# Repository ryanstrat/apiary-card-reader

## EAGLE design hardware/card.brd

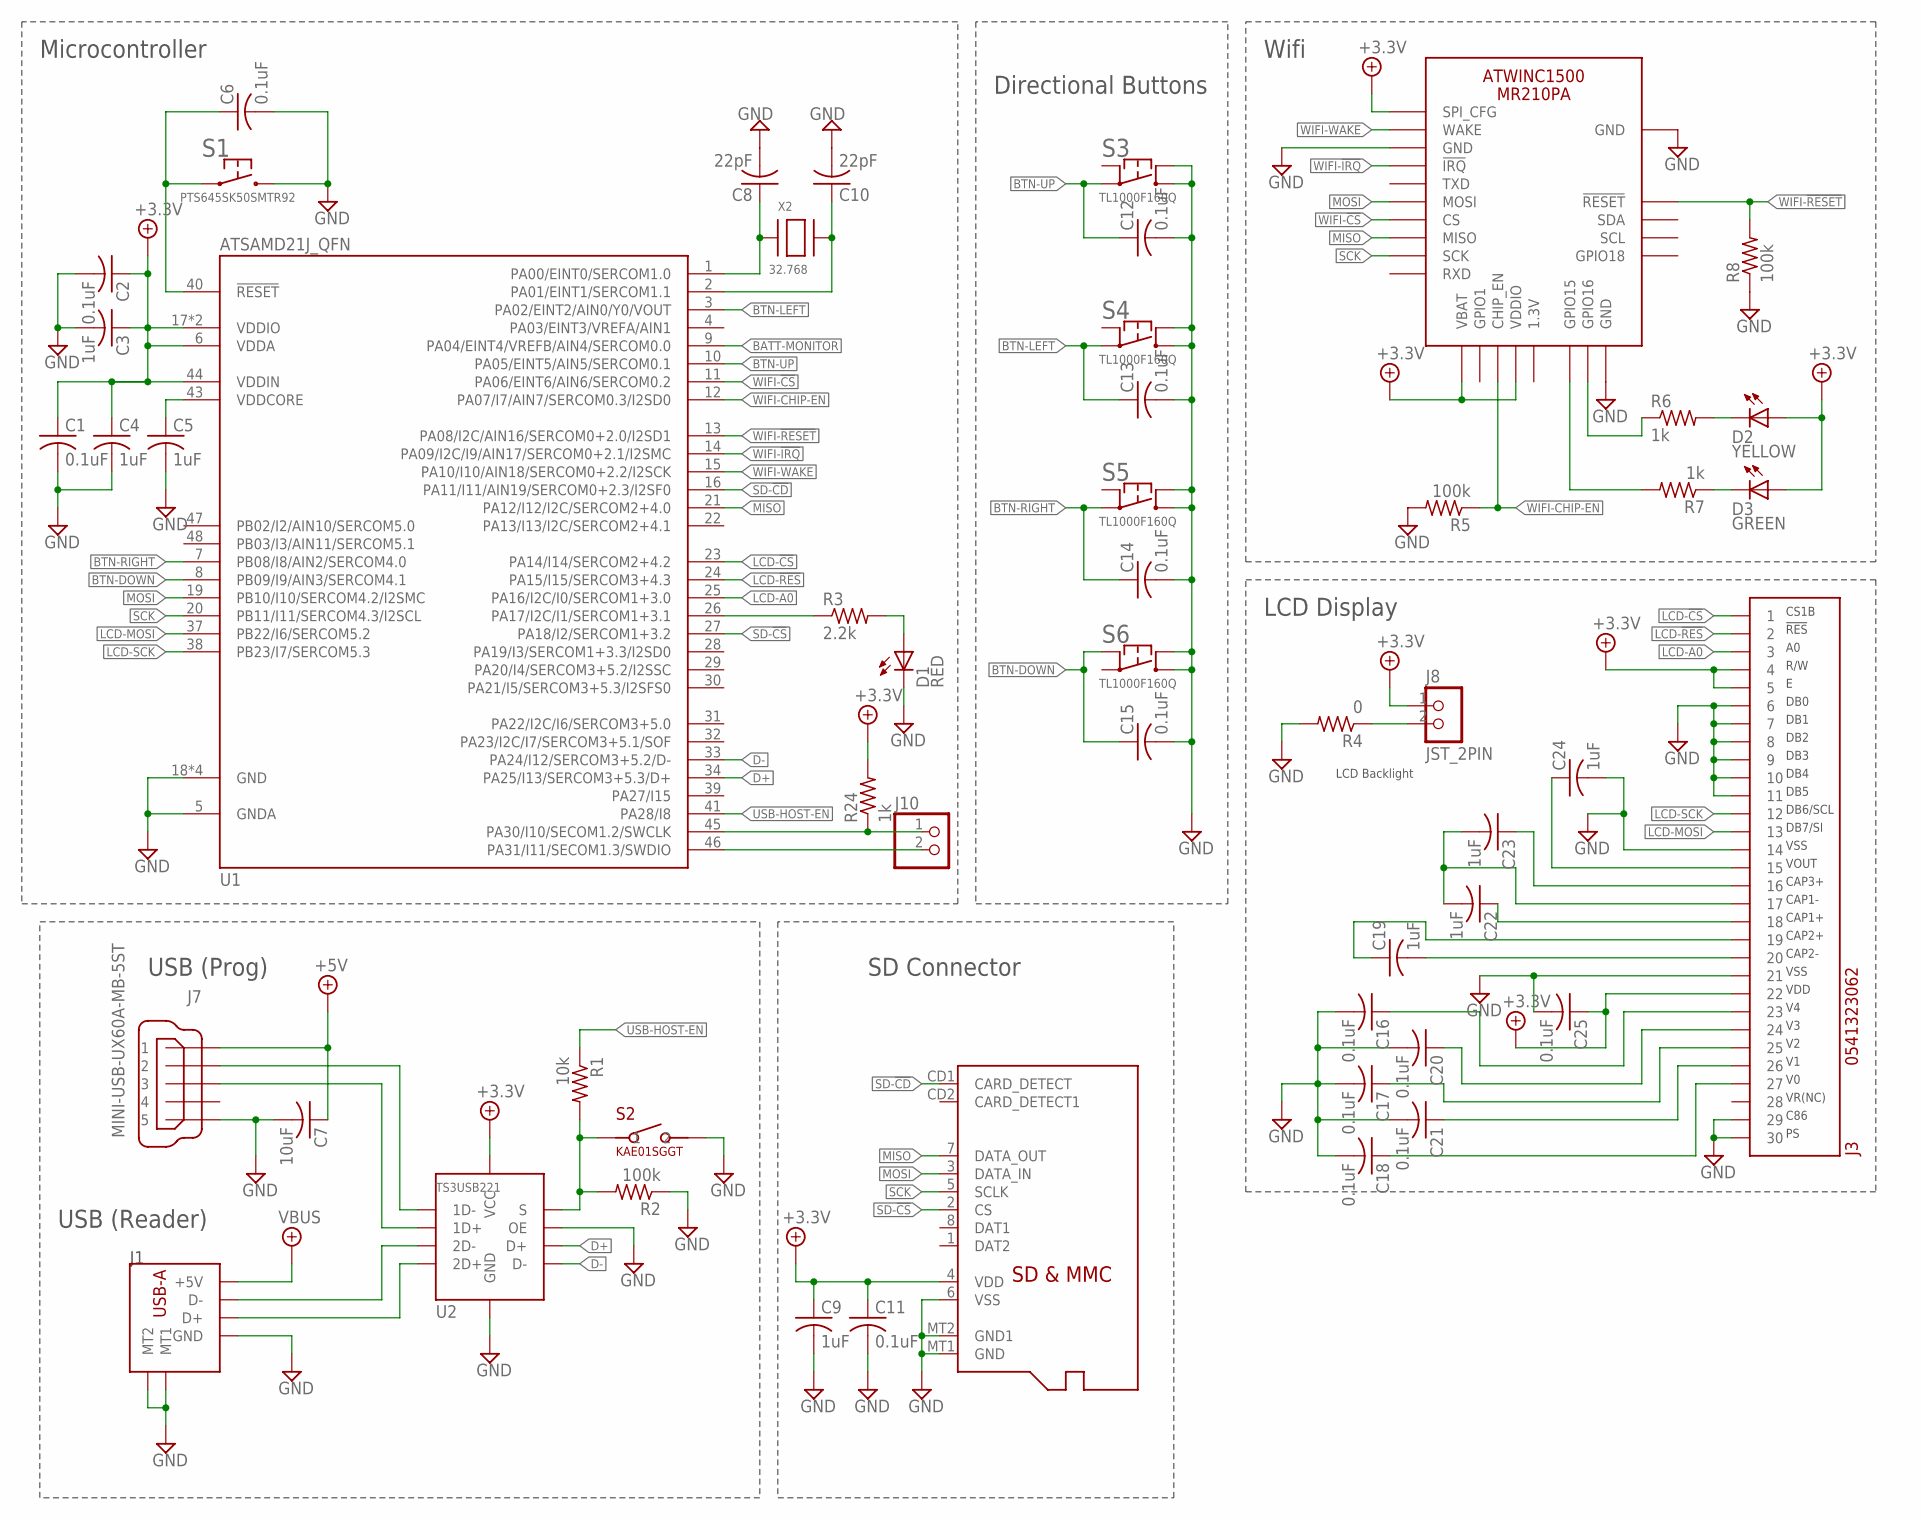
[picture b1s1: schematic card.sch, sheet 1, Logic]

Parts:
C1, C2, C6, C11, C12, C13, C14, C15, C16, C17, C18, C20, C21, C25: 0.1uF; C0603
C3, C4, C5, C9, C19, C22, C23, C24: 1uF; C0603
C7: 10uF; C0603
C8, C10: 22pF; C0603
D1: RED; CHIP-LED0603
D2: YELLOW; CHIP-LED0603
D3: GREEN; CHIP-LED0603
J1: UE27AC54100; USB-A
J2: MICROSD
J3: 0541323062
J7: MINI-USB-UX60A-MB-5ST; UX60A-MB-5ST
J8: JST_2PIN; JSTPH2
J10: CONN-2VERT; 1X2
R1: 10k; R0603
R2, R5, R8: 100k; R0603
R3: 2.2k; R0603
R4: 0; R0603
R6, R7, R24: 1k; R0603
S1: PTS645SK50SMTR92
S2: KAE01SGGT
S3, S4, S5, S6: TL1000F160Q; TL1100
U1: ATSAMD21J_QFN; TQFN48_7MM
U2: TS3USB221; 10-PIN-UQFN
X2: 32.768; XTAL3215
X3: ATWINC1500_MR210PA

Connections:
1D+: J7.3, U2.1 (1D+)
1D-: J7.2, U2.2 (1D-)
2D+: J1.3 (D+), U2.3 (2D+)
2D-: J1.2 (D-), U2.4 (2D-)
!RESET: C6.1, S1.1, S1.2 (1), U1.40 (!RESET)
+3.3V: C1.1, C2.1, C3.1, C4.1, C9.1, C11.1, C25.1, D2.A, D3.A, J2.4 (VDD), J3.4, J3.5, J3.22, J8.1, R24.2, U1.6 (VDDA), U1.17 (VDDIO), U1.36 (VDDIO), U1.44 (VDDIN), U2.10 (VCC), X3.J10 (SPI_CFG), X3.J20 (VBAT), X3.J23 (VDDIO); also elsewhere on the board
+5V: C7.1, J7.1; also elsewhere on the board
BATT-MONITOR: U1.9 (PA04/EINT4/VREFB/AIN4/SERCOM0.0); also elsewhere on the board
BTN-DOWN: C15.1, S6.2 (1B), U1.8 (PB09/I9/AIN3/SERCOM4.1)
BTN-LEFT: C13.1, S4.1 (1A), U1.3 (PA02/EINT2/AIN0/Y0/VOUT)
BTN-RIGHT: C14.1, S5.1 (1A), U1.7 (PB08/I8/AIN2/SERCOM4.0)
BTN-UP: C12.1, S3.1 (1A), U1.10 (PA05/EINT5/AIN5/SERCOM0.1)
D+: U1.34 (PA25/I13/SERCOM3+5.3/D+), U2.8 (D+)
D-: U1.33 (PA24/I12/SERCOM3+5.2/D-), U2.7 (D-)
GND: C1.2, C2.2, C3.2, C4.2, C5.2, C6.2, C7.2, C8.2, C9.2, C10.2, C11.2, C12.2, C13.2, C14.2, C15.2, C16.2, C17.2, C18.2, C20.2, C21.2, C24.2, C25.2, D1.C (K), J1.4 (GND), J1.MT1, J1.MT2, J2.6 (VSS), J2.MT1 (GND), J2.MT2 (GND1), J3.6, J3.7, J3.8, J3.9, J3.10, J3.11, J3.14, J3.21, J3.29, J3.30, J7.5, R2.1, R4.2, R5.2, R8.1, S1.3 (2), S1.4 (2), S2.2, S3.3 (2A), S3.4 (2B), S4.3 (2A), S4.4 (2B), S5.3 (2A), S5.4 (2B), S6.3 (2A), S6.4 (2B), U1.5 (GNDA), U1.18 (GND), U1.35 (GND), U1.42 (GND), U1.THERMAL (GND), U2.5 (GND), U2.6 (OE), X3.J9 (GND), X3.J12 (GND), X3.J28 (GND); also elsewhere on the board
LCD-!CS: J3.1, U1.23 (PA14/I14/SERCOM2+4.2)
LCD-!RES: J3.2, U1.24 (PA15/I15/SERCOM3+4.3)
LCD-A0: J3.3, U1.25 (PA16/I2C/I0/SERCOM1+3.0)
LCD-CA1+: C22.1, J3.18
LCD-CA1-: C22.2, C23.2, J3.17
LCD-CA2+: C19.1, J3.19
LCD-CA2-: C19.2, J3.20
LCD-CA3+: C23.1, J3.16
LCD-K: J8.2, R4.1
LCD-MOSI: J3.13, U1.37 (PB22/I6/SERCOM5.2)
LCD-SCK: J3.12, U1.38 (PB23/I7/SERCOM5.3)
LCD-V0: C18.1, J3.27
LCD-V1: C21.1, J3.26
LCD-V2: C17.1, J3.25
LCD-V3: C20.1, J3.24
LCD-V4: C16.1, J3.23
LCD-VOUT: C24.1, J3.15
MISO: J2.7 (DATA_OUT), U1.21 (PA12/I12/I2C/SERCOM2+4.0), X3.J17 (MISO)
MOSI: J2.3 (DATA_IN), U1.19 (PB10/I10/SERCOM4.2/I2SMC), X3.J15 (MOSI)
PROG-LED: D1.A, R3.2
PROG-LED-2: R3.1, U1.26 (PA17/I2C/I1/SERCOM1+3.1)
SCK: J2.5 (SCLK), U1.20 (PB11/I11/SERCOM4.3/I2SCL), X3.J18 (SCK)
SD-!CD: J2.CD1 (CARD_DETECT), U1.16 (PA11/I11/AIN19/SERCOM0+2.3/I2SF0)
SD-!CS: J2.2 (CS), U1.27 (PA18/I2/SERCOM1+3.2)
SWCLK: J10.1, R24.1, U1.45 (PA30/I10/SECOM1.2/SWCLK)
SWDIO: J10.2, U1.46 (PA31/I11/SECOM1.3/SWDIO)
USB-HOST-EN: R1.1, U1.41 (PA28/I8)
USB-S: R1.2, R2.2, S2.1, U2.9 (S)
VBUS: J1.1 (+5V); also elsewhere on the board
VDDCORE: C5.1, U1.43 (VDDCORE)
WIFI-!CS: U1.11 (PA06/EINT6/AIN6/SERCOM0.2), X3.J16 (CS)
WIFI-!IRQ: U1.14 (PA09/I2C/I9/AIN17/SERCOM0+2.1/I2SMC), X3.J13 (!IRQ)
WIFI-!RESET: R8.2, U1.13 (PA08/I2C/AIN16/SERCOM0+2.0/I2SD1), X3.J4 (!RESET)
WIFI-CHIP-EN: R5.1, U1.12 (PA07/I7/AIN7/SERCOM0.3/I2SD0), X3.J22 (CHIP_EN)
WIFI-GPIO15: R7.2, X3.J26 (GPIO15)
WIFI-GPIO16: R6.1, X3.J27 (GPIO16)
WIFI-LED-G: D3.C (K), R7.1
WIFI-LED-Y: D2.C (K), R6.2
WIFI-WAKE: U1.15 (PA10/I10/AIN18/SERCOM0+2.2/I2SCK), X3.J11 (WAKE)
X3-1: C8.1, U1.1 (PA00/EINT0/SERCOM1.0), X2.P$1
X3-2: C10.1, U1.2 (PA01/EINT1/SERCOM1.1), X2.P$2

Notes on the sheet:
Microcontroller
USB (Prog)
SD Connector
USB (Reader)
Wifi
Directional Buttons
CS1B
!RES
R/W
DB0
DB1
DB2
DB3
DB4
DB5
DB6/SCL
DB7/SI
VSS
VOUT
CAP3+
CAP1-
CAP1+
CAP2+
CAP2-
VDD
VR(NC)
C86
LCD Display
LCD Backlight

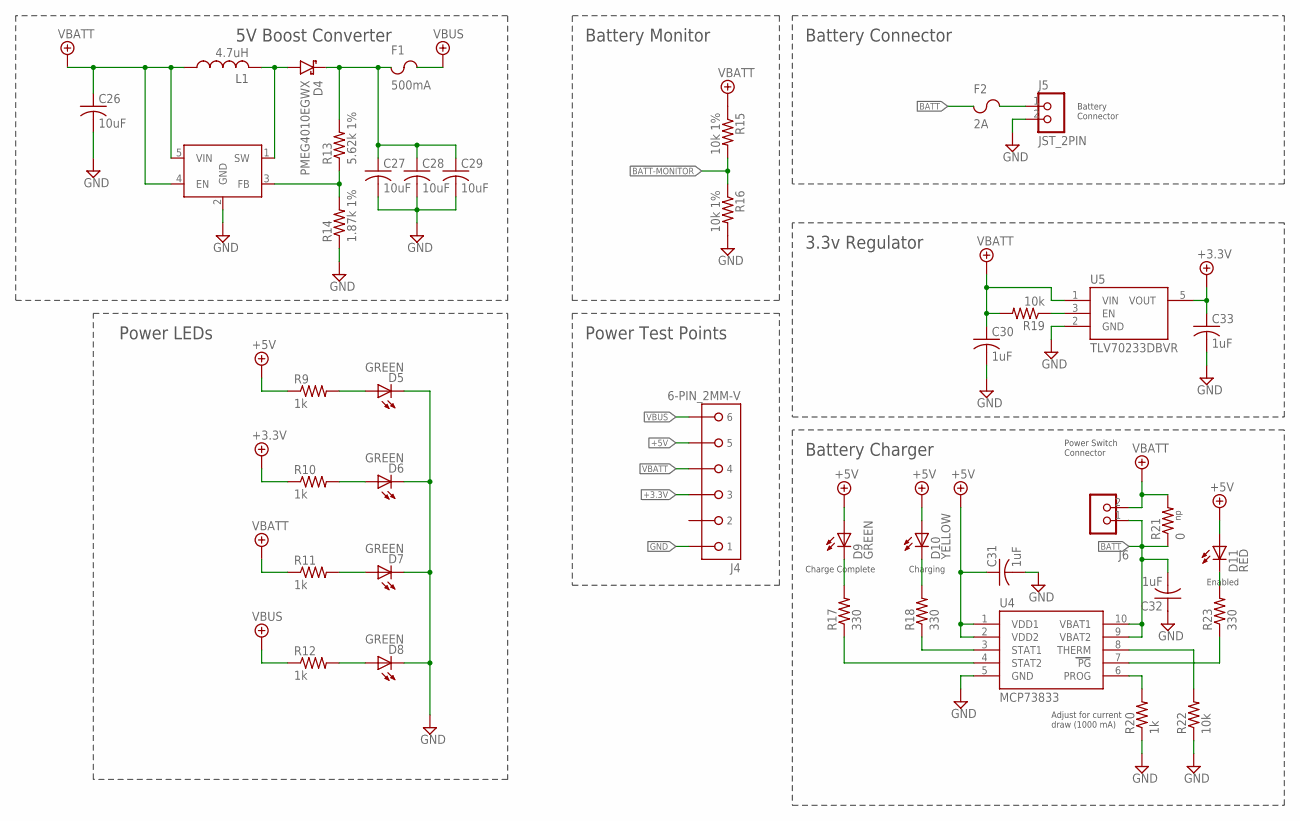
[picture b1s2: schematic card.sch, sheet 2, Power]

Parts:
C26, C27, C28, C29: 10uF; C0603
C30, C31, C32, C33: 1uF; C0603
D4: PMEG4010EGWX; SOD123
D5, D6, D7, D8, D9: GREEN; CHIP-LED0603
D10: YELLOW; CHIP-LED0603
D11: RED; CHIP-LED0603
F1: 500mA; F0603
F2: 2A; F0603
J4: 6-PIN_2MM-V; 2MM-6-V
J5, J6: JST_2PIN; JSTPH2
L1: 4.7uH; L0805
R9, R10, R11, R12, R20: 1k; R0603
R13: 5.62k 1%; R0603
R14: 1.87k 1%; R0603
R15, R16: 10k 1%; R0603
R17, R18, R23: 330; R0603
R19, R22: 10k; R0603
R21: 0; R0603
U3: MIC2288YD5-TR; TSOT-23-5
U4: MCP73833; MSOP10
U5: TLV70233DBVR; SOT-23-5

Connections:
3V3_EN: R19.1, U5.3 (EN)
+3.3V: C33.1, J4.3, R10.1, U5.5 (VOUT); also elsewhere on the board
+5V: C31.1, D9.A, D10.A, D11.A, J4.5, R9.1, U4.1 (VDD1), U4.2 (VDD2); also elsewhere on the board
BATT: C32.2, F2.1, J6.1, R21.1, U4.9 (VBAT2), U4.10 (VBAT1)
BATT-MONITOR: R15.2, R16.1; also elsewhere on the board
BATT-PRE-FUSE: F2.2, J5.1
BOOST_FB: R13.1, R14.2, U3.3 (FB)
BOOST_OUTPUT: C27.1, C28.1, C29.1, D4.C, F1.1, R13.2
BOOST_SW: D4.A, L1.2, U3.1 (SW)
CHRG-!PG: R23.1, U4.7 (PG)
CHRG-PROG: R20.2, U4.6 (PROG)
CHRG-STAT1: R18.1, U4.3 (STAT1)
CHRG-STAT2: R17.1, U4.4 (STAT2)
CHRG-THERM: R22.2, U4.8 (THERM)
GND: C26.2, C27.2, C28.2, C29.2, C30.2, C31.2, C32.1, C33.2, D5.C (K), D6.C (K), D7.C (K), D8.C (K), J4.1, J5.2, R14.1, R16.2, R20.1, R22.1, U3.2 (GND), U4.5 (GND), U5.2 (GND); also elsewhere on the board
LED-3V3: D6.A, R10.2
LED-5V: D8.A, R12.2
LED-!PG: D11.C (K), R23.2
LED-STAT1: D10.C (K), R18.2
LED-STAT2: D9.C (K), R17.2
LED-VBATT: D7.A, R11.2
LED-VBUS: D5.A, R9.2
VBATT: C26.1, C30.1, J4.4, J6.2, L1.1, R11.1, R15.1, R19.2, R21.2, U3.4 (EN), U3.5 (VIN), U5.1 (VIN)
VBUS: F1.2, J4.6, R12.1; also elsewhere on the board

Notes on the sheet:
Adjust for current draw (1000 mA)
Battery Connector
Battery Connector
3.3v Regulator
Battery Charger
Battery Monitor
Power Switch Connector
5V Boost Converter
Power Test Points
Charge Complete
Charging
Enabled
Power LEDs

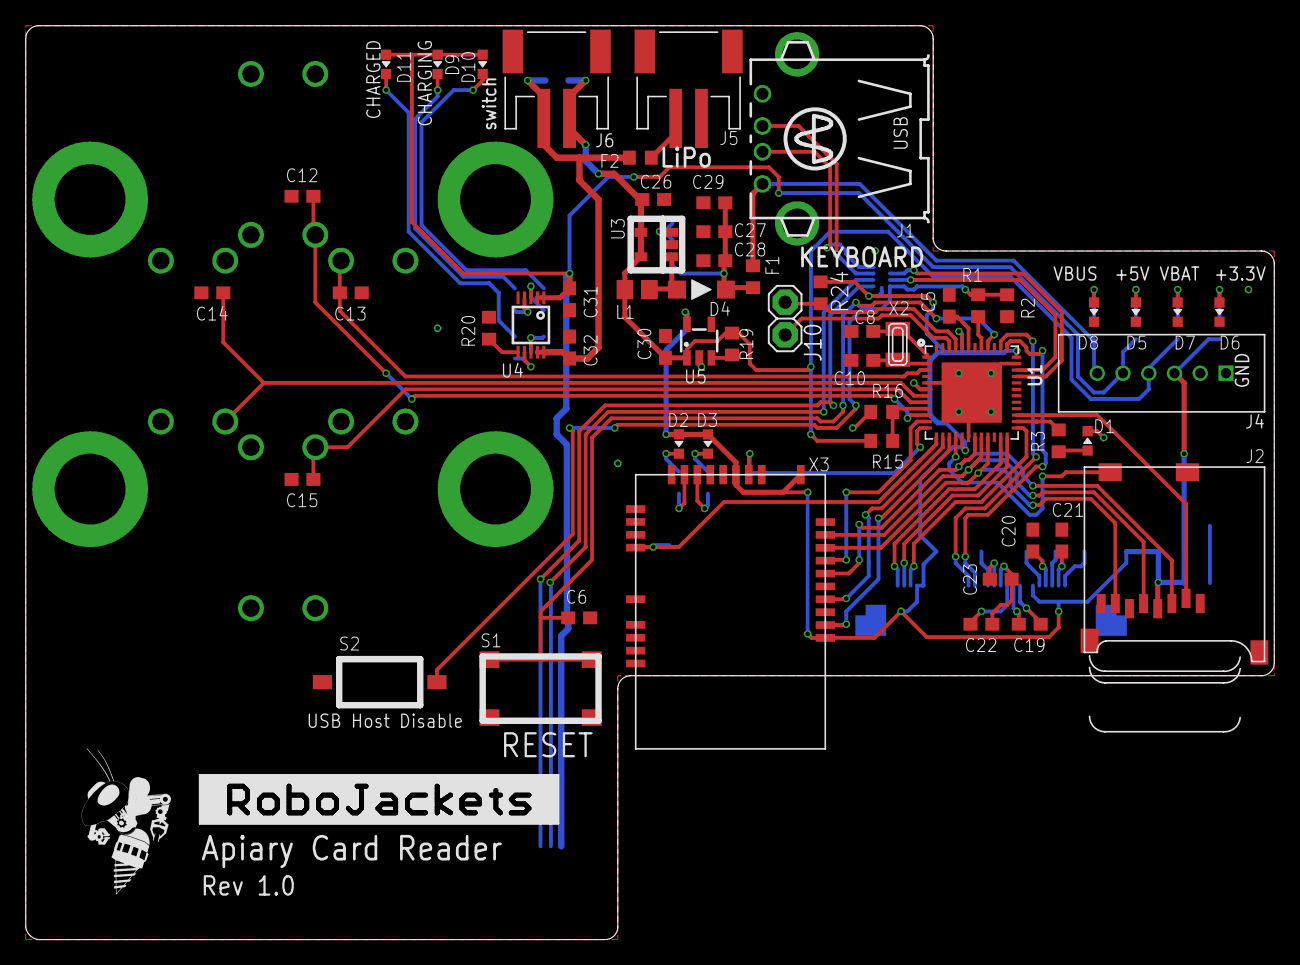
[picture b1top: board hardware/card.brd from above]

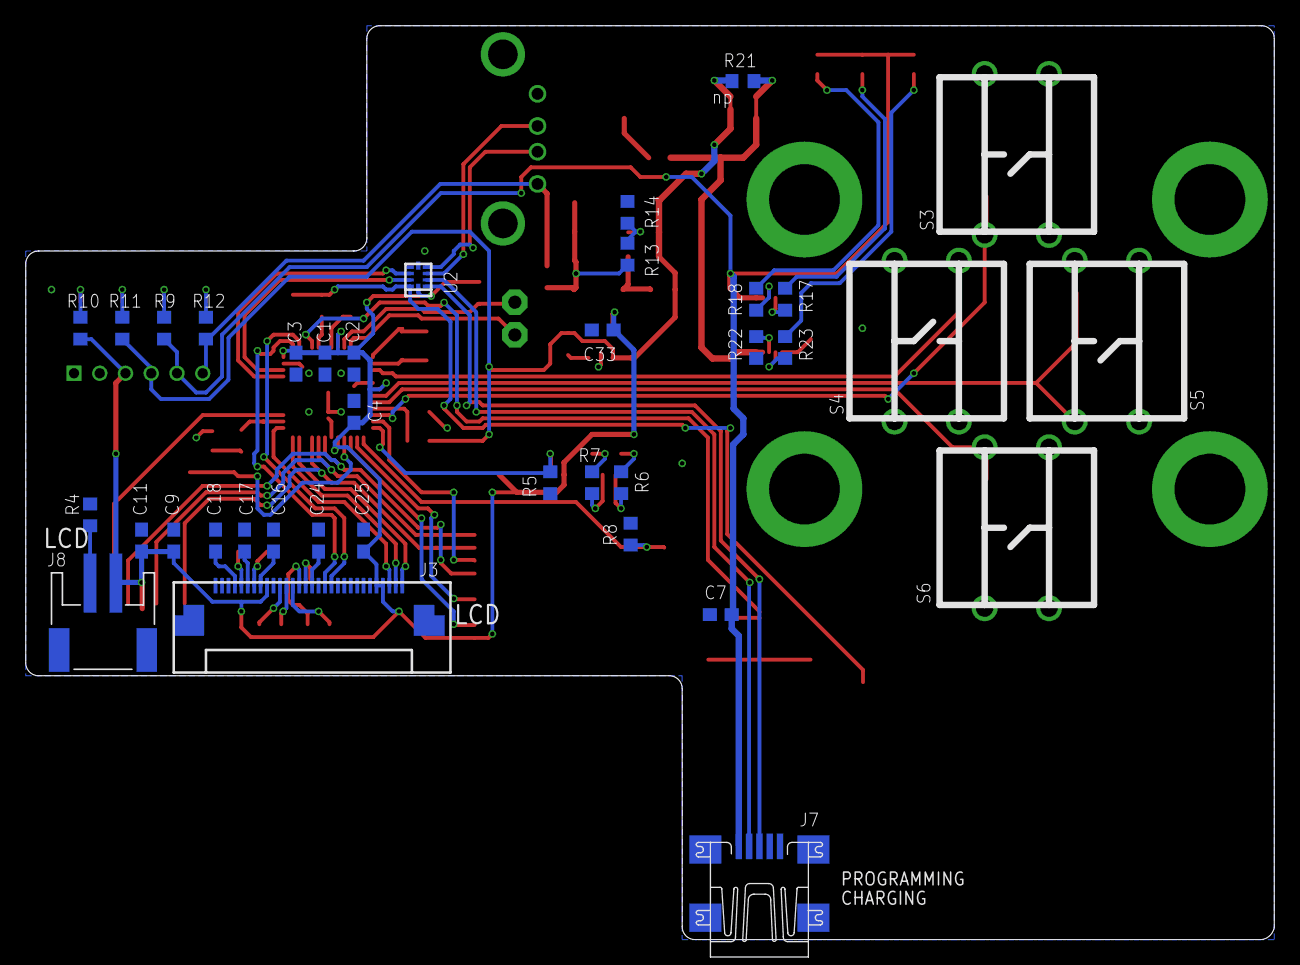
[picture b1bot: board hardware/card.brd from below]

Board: 2 copper layers, 97.0 x 71.0 mm, 95 parts (37 on the bottom side), 75 nets.

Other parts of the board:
U$1: ROBOBUZZ_0.6X
U$2: ROBOJACKETS

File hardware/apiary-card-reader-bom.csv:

"Qty";"Value";"Device";"Package";"Parts";"Description";"";
"2";"0";"R-US_R0603";"R0603";"R4, R21";"RESISTOR, American symbol";"";
"14";"0.1uF";"C-USC0603";"C0603";"C1, C2, C6, C11, C12, C13, C14, C15, C16, C17, C18, C20, C21, C25";"CAPACITOR, American symbol";"";
"1";"0541323062";"0541323062";"0541323062";"J3";"30 Position FFC, FPC Connector Contacts, Bottom 0.020" (0.50mm) Surface Mount, Right Angle";"";
"1";"1.87k 1%";"R-US_R0603";"R0603";"R14";"RESISTOR, American symbol";"";
"3";"100k";"R-US_R0603";"R0603";"R2, R5, R8";"RESISTOR, American symbol";"";
"3";"10k";"R-US_R0603";"R0603";"R1, R19, R22";"RESISTOR, American symbol";"";
"2";"10k 1%";"R-US_R0603";"R0603";"R15, R16";"RESISTOR, American symbol";"";
"4";"10uF";"C-USC0603";"C0603";"C26, C27, C28, C29";"CAPACITOR, American symbol";"";
"1";"10uF";"C-USC0805";"C0805";"C7";"CAPACITOR, American symbol";"";
"7";"1k";"R-US_R0603";"R0603";"R6, R7, R9, R10, R11, R12, R20";"RESISTOR, American symbol";"";
"12";"1uF";"C-USC0603";"C0603";"C3, C4, C5, C9, C19, C22, C23, C24, C30, C31, C32, C33";"CAPACITOR, American symbol";"";
"1";"2.2k";"R-US_R0603";"R0603";"R3";"RESISTOR, American symbol";"";
"2";"22pF";"C-USC0603";"C0603";"C8, C10";"CAPACITOR, American symbol";"";
"1";"2A";"CHIP_FUSE0603";"F0603";"F2";"";"";
"1";"32.768";"XTAL-3.2X1.5";"XTAL3215";"X2";"Low cost SMT crystals, no capacitors included";"";
"3";"330";"R-US_R0603";"R0603";"R17, R18, R23";"RESISTOR, American symbol";"";
"1";"4.7uH";"L-US-0805";"L0805";"L1";"";"";
"1";"5.62k 1%";"R-US_R0603";"R0603";"R13";"RESISTOR, American symbol";"";
"1";"500mA";"CHIP_FUSE0603";"F0603";"F1";"";"";
"1";"6-PIN_2MM-V";"6-PIN_2MM-V";"2MM-6-V";"J4";"";"";
"1";"ATSAMD21J_QFN";"ATSAMD21J_QFN";"TQFN48_7MM";"U1";"";"";
"1";"ATWINC1500_MR210PA";"ATWINC1500_MR210PA";"ATWINC1500_MR210PA";"X3";"ATWINC1500_MR210PA wifi module";"";
"1";"B2PS-VH(LF)(SN)";"B2PS-VH(LF)(SN)";"B2PS-CENTERED";"J6";"Power Connector";"";
"6";"GREEN";"LED-SMD-GREEN";"CHIP-LED0603";"D3, D5, D6, D7, D8, D9";"";"";
"2";"JST_2PIN";"JST_2PIN";"JSTPH2";"J5, J8";"JST 2-Pin Right-Angle Connector";"";
"1";"KAE01SGGT";"KAE01SGGT";"KAE01SGGT";"S2";"";"";
"1";"MCP73833";"MCP73833";"MSOP10";"U4";"Lithium-Polymer/Lithium-Ion Battery Charger [Part No.]";"";
"1";"MIC2288YD5-TR";"MIC2288YD5-TR";"TSOT-23-5";"U3";"Boost Switching Regulator IC Positive Adjustable 2.5V 1 Output 1.2A (Switch) SOT-23-5 Thin, TSOT-23-5";"";
"1";"MICROSD";"MICROSD";"MICROSD";"J2";"Micro-SD / Transflash card holder with SPI pinout";"";
"1";"MINI-USB-UX60A-MB-5ST";"MINI-USB-UX60A-MB-5ST";"UX60A-MB-5ST";"J7";"MINI USB Connector";"";
"1";"PMEG4010EGWX";"SCHOTTKEY-DIODE-SOD123";"SOD123";"D4";"";"";
"1";"PTS645SK50SMTR92";"PTS645SK50SMTR92";"PTS645SK50SMTR92";"S1";"";"";
"2";"RED";"LED-SMD-RED";"CHIP-LED0603";"D1, D11";"";"";
"4";"TL1000F160Q";"TL1000F160Q";"TL1100";"S3, S4, S5, S6";"Tactile Switch SPST-NO Top Actuated Through Hole";"";
"1";"TLV70233DBVR";"TLV70233DBVR";"SOT-23-5";"U5";"";"";
"1";"TS3USB221";"TS3USB221";"10-PIN-UQFN";"U2";"High Speed USB 2.0 1:2 MUX-DEMUX switch with single enable";"";
"1";"UE27AC54100";"UE27AC54100";"USB-A";"J1";"";"";
"2";"YELLOW";"LED-SMD-YELLOW";"CHIP-LED0603";"D2, D10";"";"";

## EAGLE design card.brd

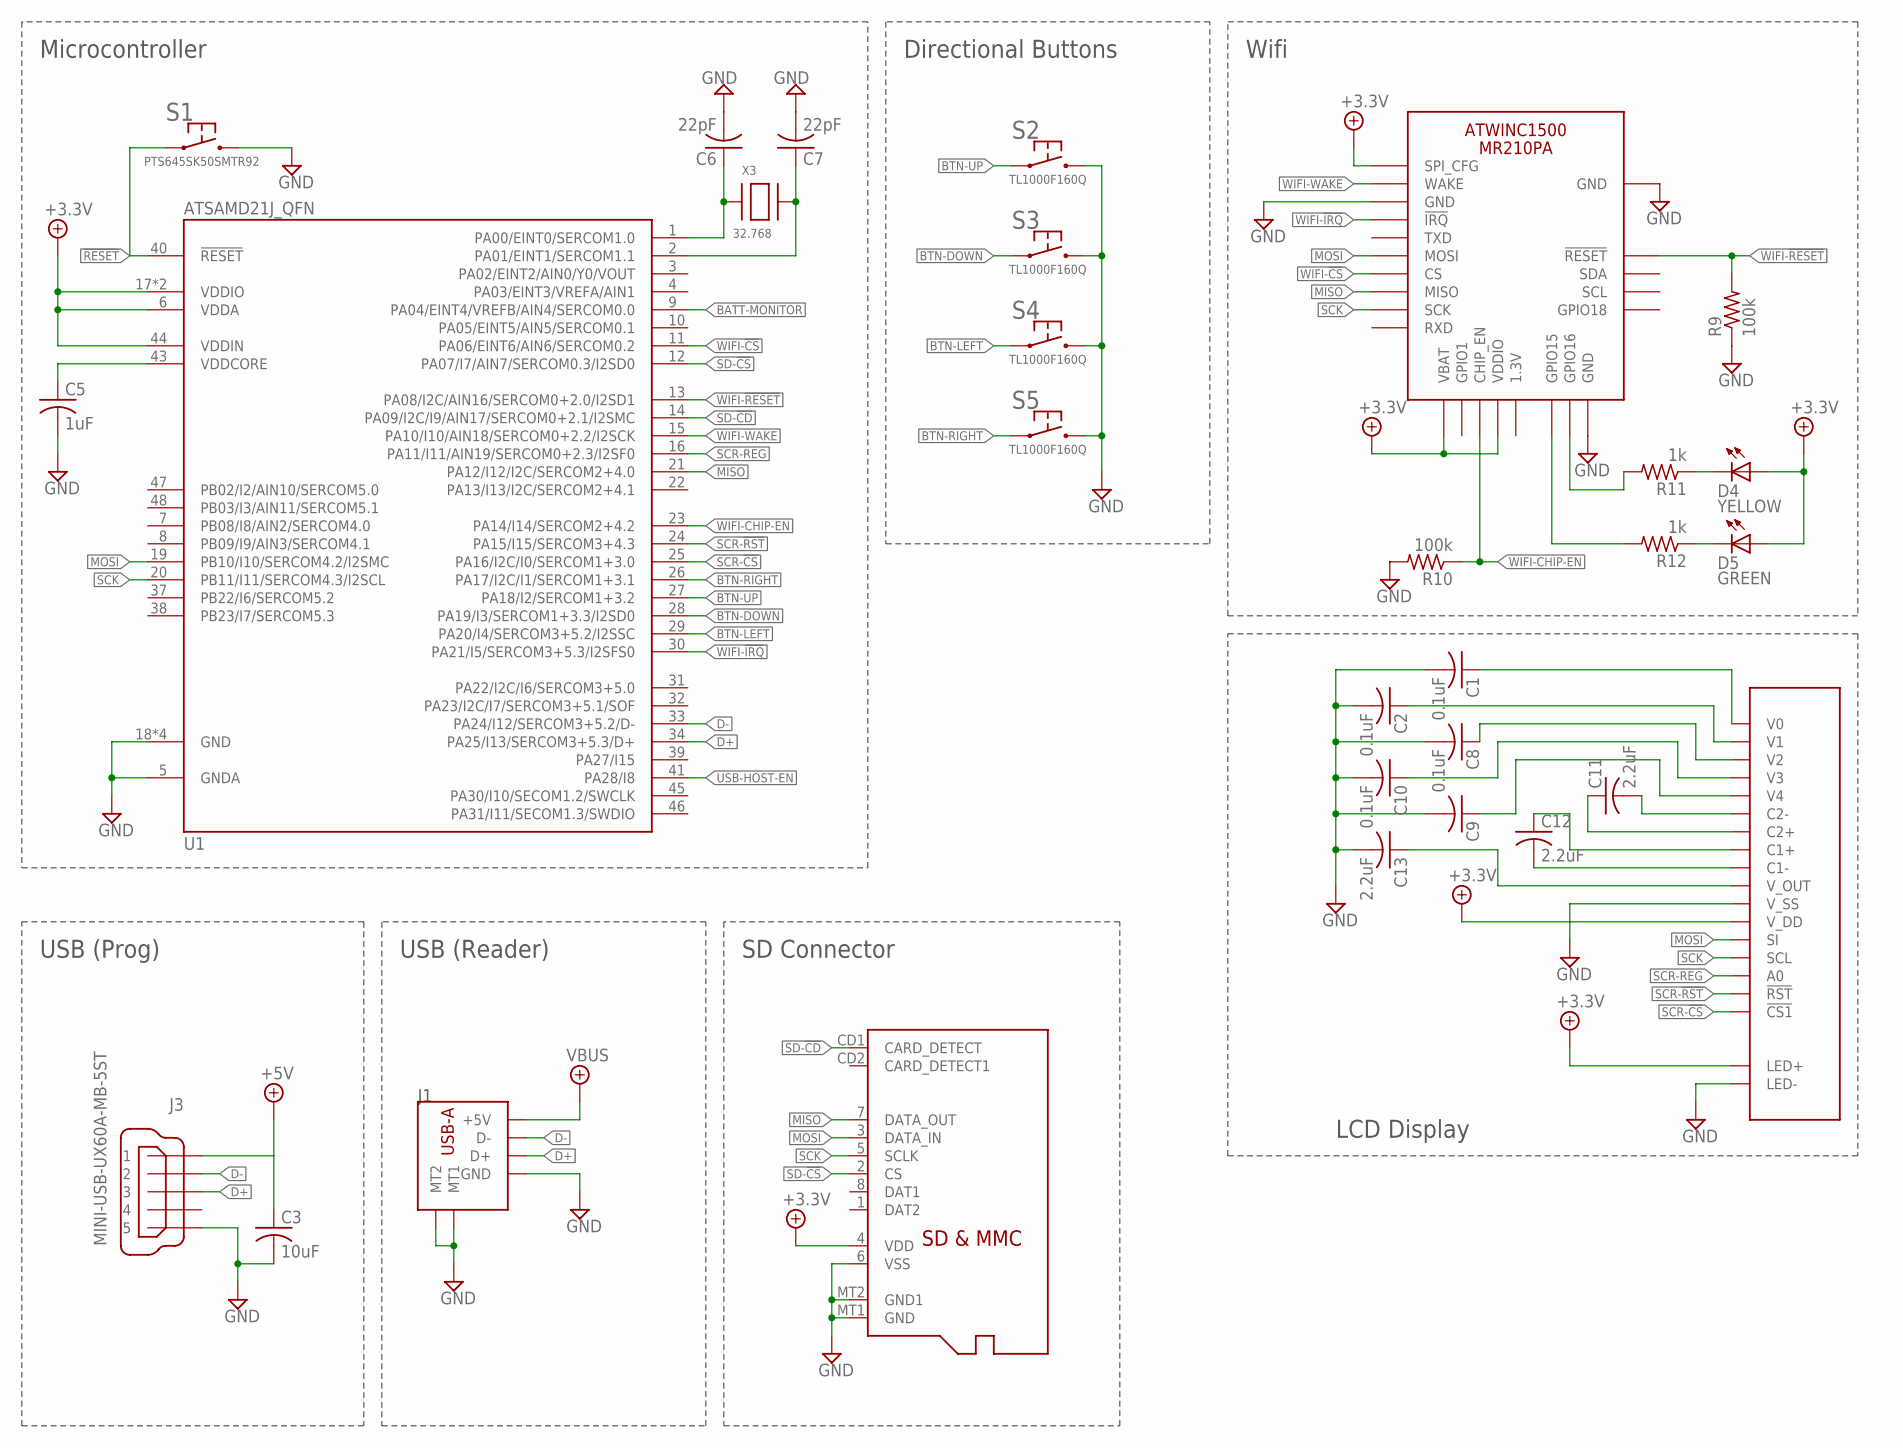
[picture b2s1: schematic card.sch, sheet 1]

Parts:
C1, C2, C8, C10: 0.1uF; C0603
C3: 10uF; C0805
C5: 1uF; C0603
C6, C7: 22pF; C0603
C9: C-USC0603; C0603
C11, C12, C13: 2.2uF; C0603
D4: YELLOW; SMARTLED-TTW
D5: GREEN; SMARTLED-TTW
J1: UE27AC54100; USB-A
J3: MINI-USB-UX60A-MB-5ST; UX60A-MB-5ST
J4: MICROSD
R9, R10: 100k; R0603W
R11, R12: 1k; R0603W
S1: PTS645SK50SMTR92
S2, S3, S4, S5: TL1000F160Q; TL1100
U1: ATSAMD21J_QFN; TQFN48_7MM
U4: ATWINC1500_MR210PA
U5: NHD-C12832A1Z-FSW-FBW-3V3
X3: 32.768; XTAL3215

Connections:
!RESET: S1.1, S1.2 (1), U1.40 (!RESET)
+3.3V: D4.A@1 (A), D5.A@1 (A), J4.4 (VDD), U1.6 (VDDA), U1.17 (VDDIO), U1.36 (VDDIO), U1.44 (VDDIN), U4.J10 (SPI_CFG), U4.J20 (VBAT), U4.J23 (VDDIO), U5.LED+, U5.V_DD; also elsewhere on the board
BATT-MONITOR: U1.9 (PA04/EINT4/VREFB/AIN4/SERCOM0.0); also elsewhere on the board
BTN-DOWN: S3.1, S3.2 (1), U1.28 (PA19/I3/SERCOM1+3.3/I2SD0)
BTN-LEFT: S4.1, S4.2 (1), U1.29 (PA20/I4/SERCOM3+5.2/I2SSC)
BTN-RIGHT: S5.1, S5.2 (1), U1.26 (PA17/I2C/I1/SERCOM1+3.1)
BTN-UP: S2.1, S2.2 (1), U1.27 (PA18/I2/SERCOM1+3.2)
D+: J1.3 (D+), J3.3, U1.34 (PA25/I13/SERCOM3+5.3/D+)
D-: J1.2 (D-), J3.2, U1.33 (PA24/I12/SERCOM3+5.2/D-)
GND: C1.2, C2.2, C3.2, C5.2, C6.2, C7.2, C8.2, C9.2, C10.2, C13.2, J1.4 (GND), J1.MT1, J1.MT2, J3.5, J4.6 (VSS), J4.MT1 (GND), J4.MT2 (GND1), R9.1 (PIN1), R10.2 (PIN2), S1.3 (2), S1.4 (2), S2.3 (2), S2.4 (2), S3.3 (2), S3.4 (2), S4.3 (2), S4.4 (2), S5.3 (2), S5.4 (2), U1.5 (GNDA), U1.18 (GND), U1.35 (GND), U1.42 (GND), U1.THERMAL (GND), U4.J9 (GND), U4.J12 (GND), U4.J28 (GND), U5.LED-, U5.V_SS; also elsewhere on the board
MISO: J4.7 (DATA_OUT), U1.21 (PA12/I12/I2C/SERCOM2+4.0), U4.J17 (MISO)
MOSI: J4.3 (DATA_IN), U1.19 (PB10/I10/SERCOM4.2/I2SMC), U4.J15 (MOSI), U5.SI
unnamed: R11.2 (PIN2), U4.J27 (GPIO16)
unnamed: R12.2 (PIN2), U4.J26 (GPIO15)
unnamed: C5.1, U1.43 (VDDCORE)
unnamed: C6.1, U1.1 (PA00/EINT0/SERCOM1.0), X3.P$1
unnamed: C7.1, U1.2 (PA01/EINT1/SERCOM1.1), X3.P$2
unnamed: D4.C@1 (C), R11.1 (PIN1)
unnamed: D5.C@1 (C), R12.1 (PIN1)
unnamed: C1.1, U5.V0
unnamed: C8.1, U5.V2
unnamed: C10.1, U5.V3
unnamed: C2.1, U5.V1
unnamed: C9.1, U5.V4
unnamed: C11.1, U5.C2+
unnamed: C11.2, U5.C2-
unnamed: C13.1, U5.V_OUT
unnamed: C12.2, U5.C1-
unnamed: C3.1, J3.1
SCK: J4.5 (SCLK), U1.20 (PB11/I11/SERCOM4.3/I2SCL), U4.J18 (SCK), U5.SCL
SCR-!CS: U1.25 (PA16/I2C/I0/SERCOM1+3.0), U5.!CS1
SCR-!RST: U1.24 (PA15/I15/SERCOM3+4.3), U5.!RST
SCR-REG: U1.16 (PA11/I11/AIN19/SERCOM0+2.3/I2SF0), U5.A0
SD-!CD: J4.CD1 (CARD_DETECT), U1.14 (PA09/I2C/I9/AIN17/SERCOM0+2.1/I2SMC)
SD-!CS: J4.2 (CS), U1.12 (PA07/I7/AIN7/SERCOM0.3/I2SD0)
USB-HOST-EN: U1.41 (PA28/I8)
VBUS: J1.1 (+5V); also elsewhere on the board
WIFI-!CS: U1.11 (PA06/EINT6/AIN6/SERCOM0.2), U4.J16 (CS)
WIFI-!IRQ: U1.30 (PA21/I5/SERCOM3+5.3/I2SFS0), U4.J13 (!IRQ)
WIFI-!RESET: R9.2 (PIN2), U1.13 (PA08/I2C/AIN16/SERCOM0+2.0/I2SD1), U4.J4 (!RESET)
WIFI-CHIP-EN: R10.1 (PIN1), U1.23 (PA14/I14/SERCOM2+4.2), U4.J22 (CHIP_EN)
WIFI-WAKE: U1.15 (PA10/I10/AIN18/SERCOM0+2.2/I2SCK), U4.J11 (WAKE)

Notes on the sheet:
Microcontroller
USB (Prog)
SD Connector
USB (Reader)
LCD Display
Wifi
Directional Buttons

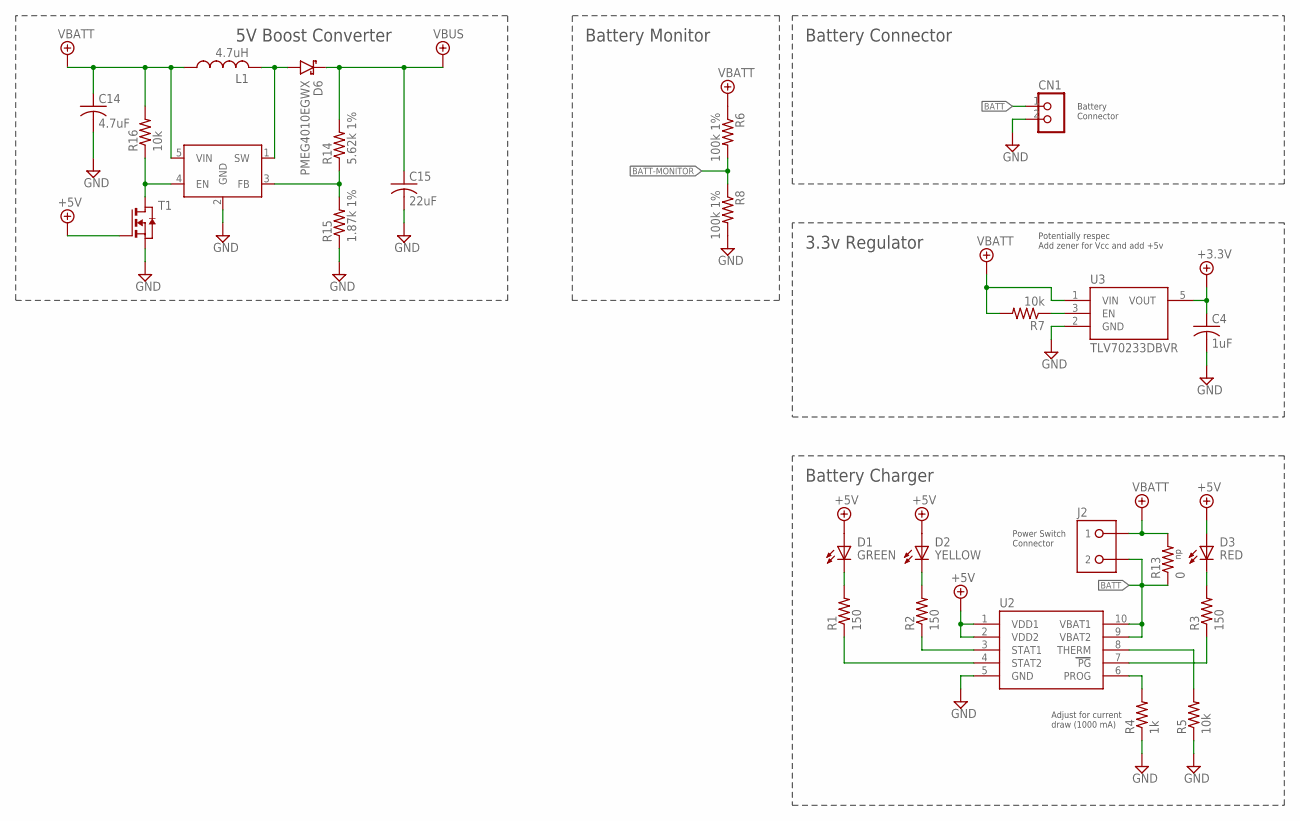
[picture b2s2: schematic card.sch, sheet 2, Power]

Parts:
C4: 1uF; C0603
C14: 4.7uF; C0603
C15: 22uF; C0603
CN1: JST_2PIN; JSTPH2
D1: GREEN; CHIP-LED0603
D2: YELLOW; CHIP-LED0603
D3: RED; CHIP-LED0603
D6: PMEG4010EGWX; SOD123
J2: B2PS-VH(LF)(SN); B2PS-CENTERED
L1: 4.7uH; L0805
R1, R2, R3: 150; R0603
R4: 1k; R0603
R5, R7, R16: 10k; R0603
R6, R8: 100k 1%; R0603
R13: 0; R0603
R14: 5.62k 1%; R0603
R15: 1.87k 1%; R0603
T1: BSS138; SOT-23
U2: MCP73833; MSOP10
U3: TLV70233DBVR; SOT-23-5
U6: MIC2288YD5-TR; TSOT-23-5

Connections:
3V3_EN: R7.1, U3.3 (EN)
+3.3V: C4.1, U3.5 (VOUT); also elsewhere on the board
+5V: D1.A, D2.A, D3.A, T1.3 (G), U2.1 (VDD1), U2.2 (VDD2)
BATT: CN1.1, J2.2, R13.1, U2.9 (VBAT2), U2.10 (VBAT1)
BATT-MONITOR: R6.2, R8.1; also elsewhere on the board
BOOST_ENABLE: R16.1, T1.1 (D), U6.4 (EN)
BOOST_FB: R14.1, R15.2, U6.3 (FB)
BOOST_SW: D6.A, L1.2, U6.1 (SW)
GND: C4.2, C14.2, C15.2, CN1.2, R4.1, R5.1, R8.2, R15.1, T1.2 (S), U2.5 (GND), U3.2 (GND), U6.2 (GND); also elsewhere on the board
unnamed: D1.C (K), R1.2
unnamed: D2.C (K), R2.2
unnamed: R2.1, U2.3 (STAT1)
unnamed: R1.1, U2.4 (STAT2)
unnamed: R3.1, U2.7 (PG)
unnamed: D3.C (K), R3.2
unnamed: R4.2, U2.6 (PROG)
unnamed: R5.2, U2.8 (THERM)
VBATT: C14.1, J2.1, L1.1, R6.1, R7.2, R13.2, R16.2, U3.1 (VIN), U6.5 (VIN)
VBUS: C15.1, D6.C, R14.2; also elsewhere on the board

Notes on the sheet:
Adjust for current draw (1000 mA)
Battery Connector
Battery Connector
3.3v Regulator
Battery Charger
Potentially respec Add zener for Vcc and add +5v
Battery Monitor
Power Switch Connector
5V Boost Converter

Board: 2 copper layers, 56 parts (0 on the bottom side), 56 nets, no tracks yet.

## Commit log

2017-11-09 cleaning up
2017-11-09 Add directional buttons, conect pins to MCU, delete scr file
2017-11-10 add framing for software components. Design review schematic tweaks
2017-11-14 Schematic Finished
2017-11-14 add Library
2017-11-14 Added power test points and LEDs
2017-11-14 halfway through routing
2017-11-15 basically done routing attempt 1
2017-11-15 board routing attempt 2
2017-11-15 silkscreen additions, fixed button labels
2017-11-15 More tweaks, fix DRC error
2017-11-15 Increase board size to put USB-B port at the edge of the case
2017-11-15 label U2
2017-11-15 fix a cap with the wrong footprint
2017-11-16 exported gerbers
    swapped the power switch connector
2017-11-30 start of validation software, case designs
2017-11-30 removed display test code
2017-11-30 uncomment code
2017-12-04 fix positioning of display and mounting holes on case top and bottom
2017-12-05 Reads config file from sd for network settings and connects to wifi Reads buzzcards Sends gtids to Apiary (unsuccessfully)
2017-12-05 Writes gtids to SD card
2017-12-05 Added menu functionality Only writes to SD card and not Apiary
